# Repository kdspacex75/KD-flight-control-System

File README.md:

# KD-flight-control-System 🚀
A custom PCB flight control system based on the STM32F103 microcontroller, designed in KiCad for experimental rocket projects. Includes USB interface, 3.3V power regulation, oscillator, and breakouts for sensors and actuators.

This repository contains the PCB design for a **flight control system** built around the **STM32F103C8T6** microcontroller.  
The board is designed in **KiCad** and intended for use in experimental rocket projects.

## ✨ Features
- STM32F103C8T6 MCU  
- USB interface for programming & communication  
- AMS1117-3.3 voltage regulator  
- Crystal oscillator (16 MHz)  
- Breakouts for USART, I²C, BOOT/RESET, GPIO  
- Mounting holes for integration into rocket frame  

## 📂 Contents
- `pcb/` – KiCad project files  
- `schematic/` – Circuit schematics  
- `renders/` – PCB 3D and layout images  

## 📸 Preview
pcb - https://github.com/kdspacex75/KD-flight-control-System/blob/main/pcb%20.png

3d image - https://github.com/kdspacex75/KD-flight-control-System/blob/main/3d%20image.png

Schematic - https://github.com/kdspacex75/KD-flight-control-System/blob/main/Schematic.pdf

## ⚡ Future Work
- Firmware development with STM32CubeIDE  
- Flight software integration  
- Sensor + actuator expansion  

---
Made with  using KiCad

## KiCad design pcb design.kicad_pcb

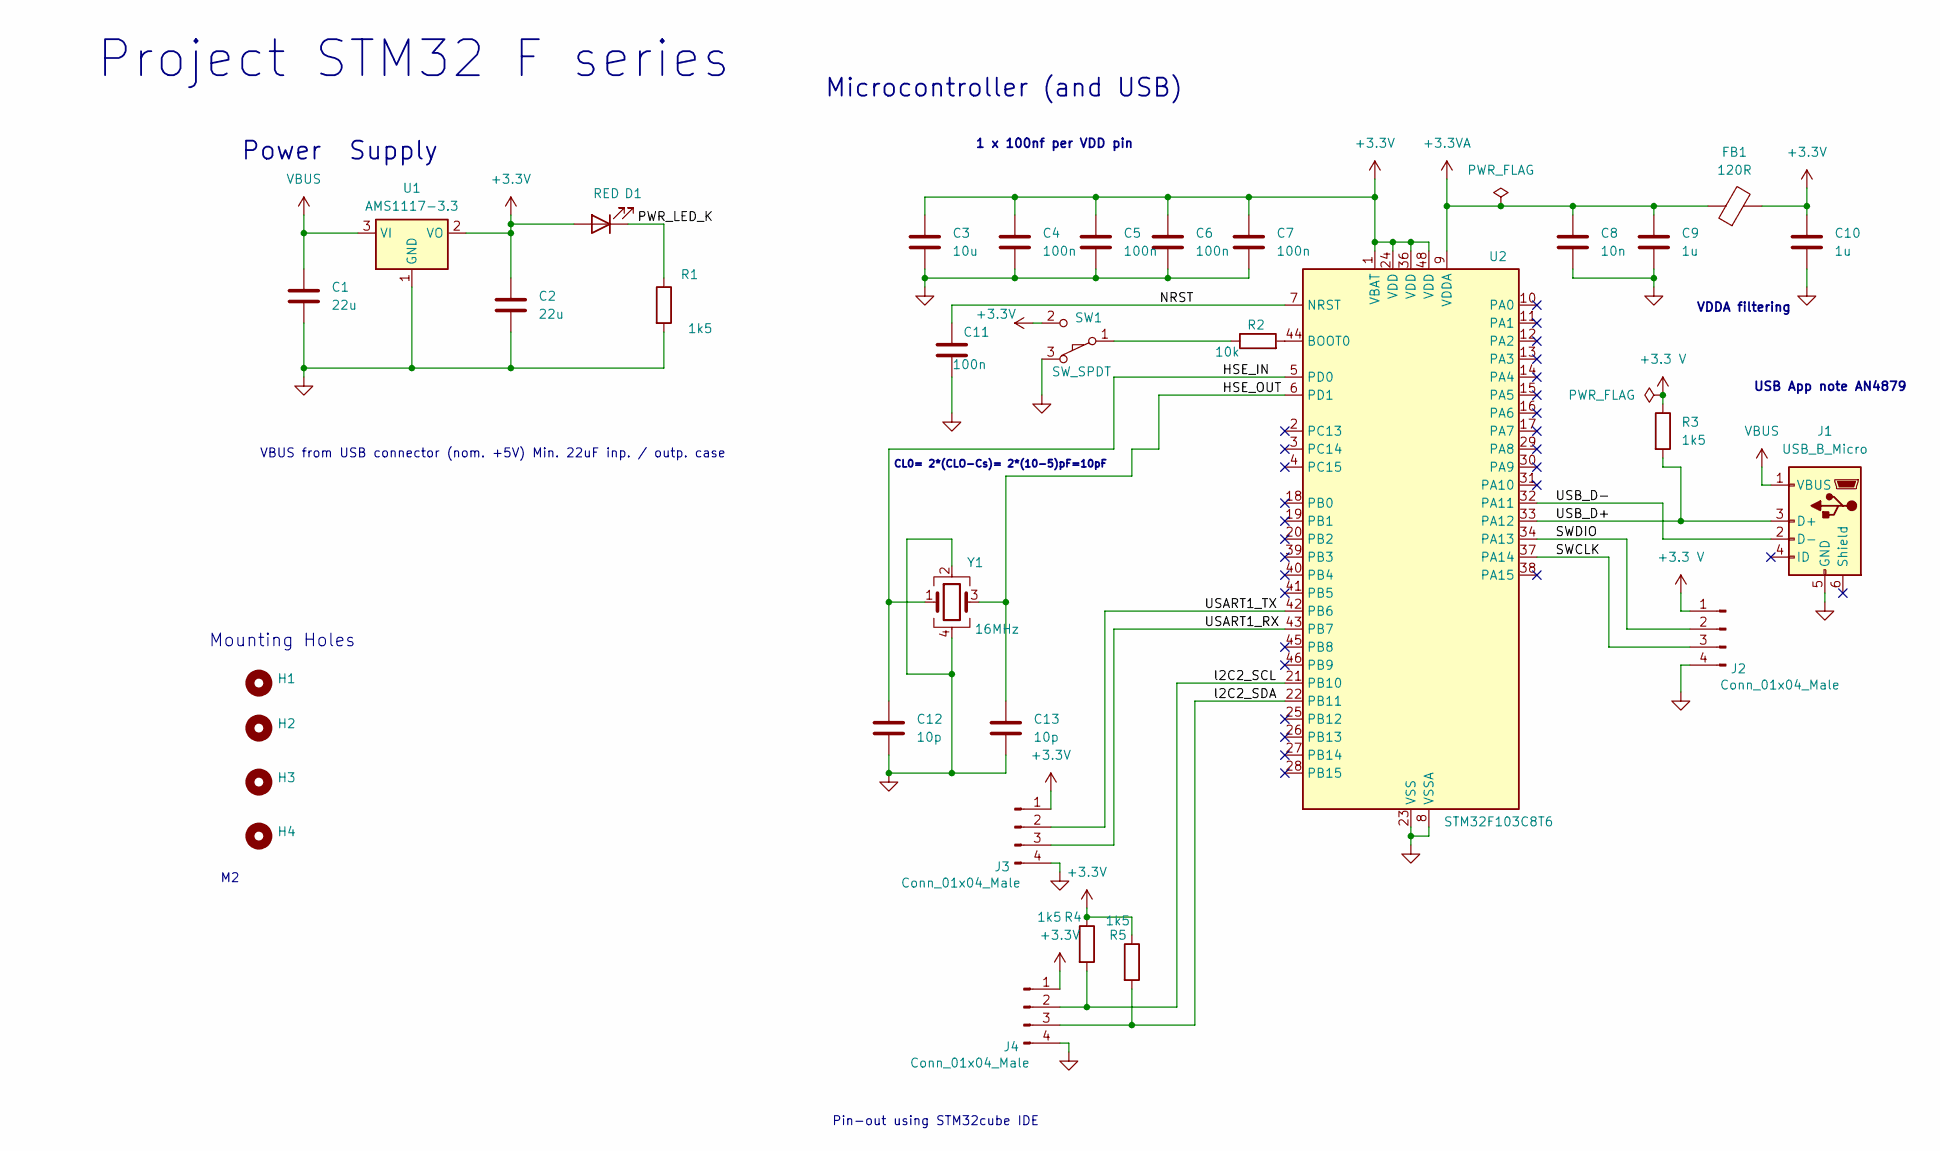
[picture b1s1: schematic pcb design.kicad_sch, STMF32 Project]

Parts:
C1, C2: 22u; C_0805_2012Metric
C3: 10u; C_0603_1608Metric
C4, C5, C6, C7, C11: 100n; C_0402_1005Metric
C8: 10n; C_0402_1005Metric
C9, C10: 1u; C_0402_1005Metric
C12, C13: 10p; C_0402_1005Metric
D1: RED; LED_0603_1608Metric
FB1: 120R; L_0603_1608Metric
H1, H2, H3, H4: MountingHole_2.1mm
J1: USB_B_Micro; USB_Micro-B_Wuerth_629105150521
J2, J3, J4: Conn_01x04_Male; PinHeader_1x04_P2.54mm_Vertical
R1, R3, R4, R5: 1k5; R_0402_1005Metric
R2: 10k; R_0402_1005Metric
SW1: SW_SPDT; SW_SPDT_PCM12
U1: AMS1117-3.3; SOT-223-3_TabPin2
U2: STM32F103C8T6; LQFP-48_7x7mm_P0.5mm
Y1: 16MHz; Crystal_SMD_3225-4Pin_3.2x2.5mm

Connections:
+3.3 V: J2.1, R3.1
+3.3V: C2.1, C3.1, C4.1, C5.1, C6.1, C7.1, C10.1, D1.2 (A), FB1.2, J3.1, J4.1, R4.1, R5.1, SW1.2 (B), U1.2 (VO), U2.1 (VBAT), U2.24 (VDD), U2.36 (VDD), U2.48 (VDD)
+3.3VA: C8.1, C9.1, FB1.1, U2.9 (VDDA)
/HSE_IN: C12.1, U2.5 (PD0), Y1.1
/HSE_OUT: C13.1, U2.6 (PD1), Y1.3
/NRST: C11.1, U2.7 (NRST)
/PWR_LED_K: D1.1 (K), R1.1
/SWCLK: J2.3, U2.37 (PA14)
/SWDIO: J2.2, U2.34 (PA13)
/USART1_RX: J3.3, U2.43 (PB7)
/USART1_TX: J3.2, U2.42 (PB6)
/USB_D+: J1.3 (D+), R3.2, U2.33 (PA12)
/USB_D-: J1.2 (D-), U2.32 (PA11)
/l2C2_SCL: J4.2, R4.2, U2.21 (PB10)
/l2C2_SDA: J4.3, R5.2, U2.22 (PB11)
GND: C1.2, C2.2, C3.2, C4.2, C5.2, C6.2, C7.2, C8.2, C9.2, C10.2, C11.2, C12.2, C13.2, J1.5 (GND), J2.4, J3.4, J4.4, R1.2, SW1.3 (C), U1.1 (GND), U2.8 (VSSA), U2.23 (VSS), U2.35 (VSS), U2.47 (VSS), Y1.2, Y1.4
unnamed: R2.1, SW1.1 (A)
unnamed: R2.2, U2.44 (BOOT0)
VBUS: C1.1, J1.1 (VBUS), U1.3 (VI)

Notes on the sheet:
Project STM32 F series
VDDA filtering
CL0= 2*(CLO-Cs)= 2*(10-5)pF=10pF
Mounting Holes
Microcontroller (and USB)
1 x 100nf per VDD pin
Power Supply
VBUS from USB connector (nom. +5V) Min. 22uF inp. / outp. case
USB App note AN4879
Pin-out using STM32cube IDE

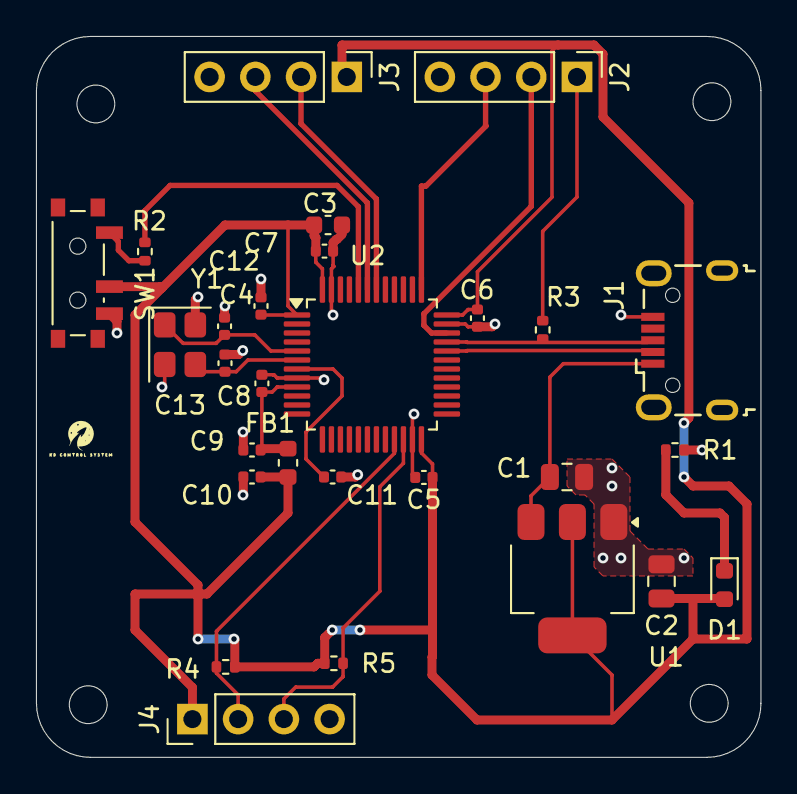
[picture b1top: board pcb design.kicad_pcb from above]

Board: 2 copper layers, 40.2 x 40.1 mm, 32 parts (0 on the bottom side), 19 nets.

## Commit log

2025-09-14 README.md
